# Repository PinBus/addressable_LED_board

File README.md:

# Addressable LED Board - Rev. 1.0

This is a small board for the WS2812B RGB and SK6812 RGBW LEDs. Either one of these LEDs can be mounted on this board as the LEDs are pin compatible.

**Warning: These designs are made as part of a hobby project and thus come with no guarantees. Do not use these designs in for any critical systems! Working with voltages higher than +40V can be potentially dangerous, please take appropriate safety measures!**

## BOM

| Identifiers | Quantity | Part |
| ----------- | -------- | ---- |
| C1          |       1x | 0805 Ceramic capacitor, 100nF |
| J1, J2      |       2x | JST XH connector, 2.5mm pitch, 3 way, through-hole |
| U1          |       1x | WS2812B _or_ SK6812 5050 LED |

## Pictures

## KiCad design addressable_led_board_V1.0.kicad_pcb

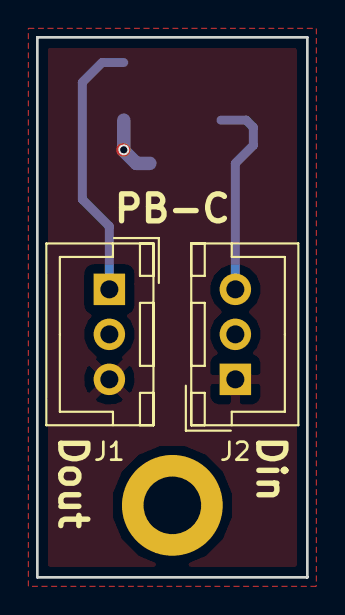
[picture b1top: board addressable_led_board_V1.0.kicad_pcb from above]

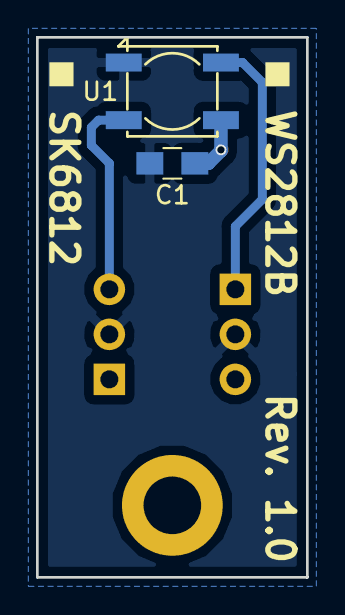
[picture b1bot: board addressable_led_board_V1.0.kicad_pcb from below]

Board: 2 copper layers, 15.0 x 30.0 mm, 4 parts (2 on the bottom side), 4 nets.

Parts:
C1: 100nF; C_0805_HandSoldering
J1, J2: CONN_01X03; JST_XH_B03B-XH-A_03x2.50mm_Straight
U1: SK6812; SK6812_HandSoldering

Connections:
unnamed: C1.1, J1.3, J2.1, U1.3
unnamed: C1.2, J1.2, J2.2, U1.1
unnamed: J1.1, U1.4
unnamed: J2.3, U1.2

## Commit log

2018-12-14 Add hardware design files
2018-12-14 Add README.md
2019-01-17 Improve documentation
